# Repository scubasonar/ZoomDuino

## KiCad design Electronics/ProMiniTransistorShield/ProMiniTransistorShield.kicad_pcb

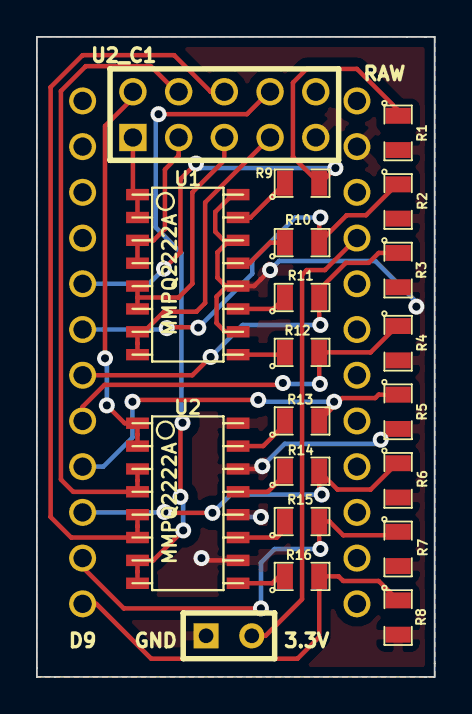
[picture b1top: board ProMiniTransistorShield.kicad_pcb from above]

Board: 2 copper layers, 22.1 x 35.6 mm, 21 parts (0 on the bottom side), 26 nets.

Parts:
IC1: ARDUINO_PRO_MINI_3V3; Arduino Pro Mini
P1: CONN_2; SIL-2
P2: CONN_5X2; PIN_ARRAY_5x2
R1, R2, R3, R4, R5, R6, R7, R8: 10K; SM0805
R9, R10, R11, R12, R13, R14, R15, R16: 1K; SM0805
U1, U2: MMPQ2222A; so-16

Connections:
3V3: IC1.16, P1.2
/D2: IC1.5, R1.1, R9.2
/D3: IC1.6, R2.1, R10.2
/D4: IC1.7, R3.1, R11.2
/D5: IC1.8, R4.1, R12.2
/D6: IC1.9, R5.1, R13.2
/D7: IC1.10, R6.1, R14.2
/D8: IC1.11, R7.1, R15.2
/D9: IC1.12, R8.1, R16.2
/U1_B1: R9.1, U1.15
/U1_B2: R10.1, U1.13
/U1_B3: R11.1, U1.11
/U1_B4: R12.1, U1.9
/U2_B1: R13.1, U2.15
/U2_B2: R14.1, U2.13
/U2_B3: R15.1, U2.11
/U2_B4: R16.1, U2.9
GND: IC1.4, IC1.14, P1.1, P2.9, P2.10, R1.2, R2.2, R3.2, R4.2, R5.2, R6.2, R7.2, R8.2, U1.10, U1.12, U1.14, U1.16, U2.10, U2.12, U2.14, U2.16
U1_C1: P2.1, U1.1, U1.2
U1_C2: P2.3, U1.3, U1.4
U1_C3: P2.5, U1.5, U1.6
U1_C4: P2.7, U1.7, U1.8
U2_C1: P2.2, U2.1, U2.2
U2_C2: P2.4, U2.3, U2.4
U2_C3: P2.6, U2.5, U2.6
U2_C4: P2.8, U2.7, U2.8

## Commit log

2014-12-20 *First commit, added transistor pro mini shield files
2014-12-20 *Added to folder structure
2014-12-20 *Added more blank project files
2014-12-20 *Added README.txt
